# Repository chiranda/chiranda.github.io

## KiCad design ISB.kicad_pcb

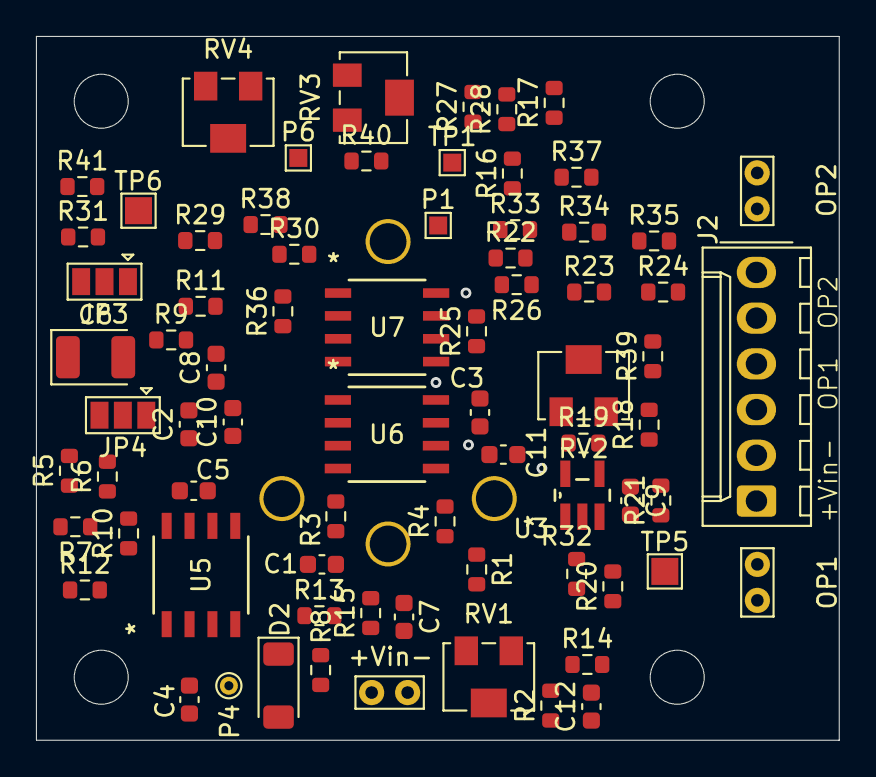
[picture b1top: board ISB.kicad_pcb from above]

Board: 2 copper layers, 44.6 x 39.1 mm, 79 parts (1 on the bottom side), 32 nets, no tracks yet.

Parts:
+Vin-: TestPoint_Bridge_Pitch2.0mm_Drill0.7mm
C1, C4: 1uF; C_0603_1608Metric
C2, C3: 220nF; C_0603_1608Metric
C5: 100nF; C_0603_1608Metric
C6: 100uF/4V; CP_EIA-3528-12_Kemet-T
C7, C9: 10nF; C_0603_1608Metric
C8, C10: 220pF; C_0603_1608Metric
C11, C12: C0805C104K5RACTU; C_0603_1608Metric
D2: D_Zener; D_MiniMELF
J2: Conn_01x06_Pin; Molex_KK-254_AE-6410-06A_1x06_P2.54mm_Vertical
J3: 7_series_sensor
JP3, JP4: SolderJumper_3_Open; SolderJumper-3_P1.3mm_Open_Pad1.0x1.5mm
M1, M2, M3, M4: MountingHole_3mm
OP1, OP2: TestPoint_Bridge_Pitch2.0mm_Drill0.7mm
P1, P6: TestPoint_Pad_1.0x1.0mm
P4: TestPoint_THTPad_D1.0mm_Drill0.5mm
R1: 10R; R_0603_1608Metric
R2, R3, R12: 10k; R_0603_1608Metric
R4, R7: 47R; R_0603_1608Metric
R5, R11, R15, R21, R29, R32, R36: 1M; R_0603_1608Metric
R6, R20, R28, R35, R37: NC; R_0603_1608Metric
R8: 22R; R_0603_1608Metric
R9: 30k; R_0603_1608Metric
R10: 220k; R_0603_1608Metric
R13, R14: 0R; R_0603_1608Metric
R16, R18: 100k; R_0603_1608Metric
R17, R19: 47k; R_0603_1608Metric
R22, R24, R26, R27: 4.7k; R_0603_1608Metric
R23, R25, R30, R39: 200k; R_0603_1608Metric
R31, R38: 180k; R_0603_1608Metric
R33, R40: 100R; R_0603_1608Metric
R34, R41: 22k; R_0603_1608Metric
RV1, RV2, RV3, RV4: NC; Potentiometer_Bourns_3214W_Vertical
TP1: TestPoint; TestPoint_Pad_1.0x1.0mm
TP5, TP6: TestPoint; TestPoint_Pad_1.5x1.5mm
U3: TLV27L1IDBVR; DBV5
U5: ISL21090BFB825Z-TK; M8_15_INR
U6, U7: LT6011ACS8-PBF; SO-8_S_LIT

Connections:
/2.5V: C5.1, C6.1, JP3.3 (B), JP4.3 (B), R9.1, R11.1, R13.1, R14.1, TP6.1, U5.6 (VOUT)
/6V: C4.1, C11.2, C12.2, D2.1 (K), P4.1, R8.1, U3.5 (VDD), U5.2 (VIN), U6.8 (V+), U7.8 (V+)
/CE: J3.1 (CNT), R1.1
/OP1: C10.2, J2.3, OP1.1, R21.1, R40.1, R41.1
/OP2: C8.2, J2.5, OP2.1, R32.2, R33.2, R34.2
/Op-Amps/U1A-: R3.2, U6.2 (-INA)
/Op-Amps/U1AO: C1.1, R1.2, TP1.1, U6.1 (OUTA)
/Op-Amps/U1B-: C3.1, R4.2, R5.2, R6.2, R18.1, U6.6 (-INB)
/Op-Amps/U1BO: C3.2, P1.1, R19.1, R20.2, R39.2, RV2.1, U6.7 (OUTB)
/Op-Amps/U2A-: C2.1, R7.2, R15.2, R16.1, U7.2 (-INA)
/Op-Amps/U2AO: C2.2, P6.1, R6.1, R17.1, R30.1, R35.1, RV1.1, U7.1 (OUTA)
/Op-Amps/U2B+: R28.2, R29.2, R30.2, U7.5 (+INB)
/Op-Amps/U2B-: C7.1, R31.2, R32.1, R35.2, U7.6 (-INB)
/Op-Amps/U2BO: C7.2, R33.1, U7.7 (OUTB)
/Op-Amps/U3+: R36.1, R37.2, R39.1, U3.3 (IN+)
/Op-Amps/U3-: C9.1, R20.1, R21.2, R38.2, U3.4 (IN-)
/Op-Amps/U3O: C9.2, R40.2, U3.1 (OUT)
/Vce: JP4.2 (C), U6.3 (+INA)
/Vin: +Vin-.1, J2.1, R8.2
/Vmid: JP3.2 (C), U6.5 (+INB), U7.3 (+INA)
/Voff: R5.1, R11.2, R12.1, R15.1
/Vpot1: R13.2, R22.1, RV3.1
/Vpot2: R14.2, R26.1, RV4.1
GND: +Vin-.1, C4.2, C5.2, C8.1, C10.1, C11.1, C12.1, D2.2 (A), J2.2, J2.4, J2.6, OP1.1, OP2.1, R10.2, R23.2, R25.2, R29.1, R34.1, R36.2, R41.2, TP5.1, U3.2 (GND), U5.4 (GND), U6.4 (V-), U7.4 (V-)
unnamed: C1.2, R2.2, R3.1
unnamed: C6.2, JP3.1 (A), JP4.1 (A), R9.2, R10.1, R12.2
unnamed: R16.2, R17.2, RV1.2, RV1.3
unnamed: R18.2, R19.2, RV2.2, RV2.3
unnamed: R22.2, R24.1, R37.1, R38.1, RV3.2
unnamed: R23.1, R24.2, RV3.3
unnamed: R25.1, R27.2, RV4.3
unnamed: R26.2, R27.1, R28.1, R31.1, RV4.2

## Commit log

2025-11-07 initial commit ISB
